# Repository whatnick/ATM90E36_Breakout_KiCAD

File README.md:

# ATM90E3x Breakout / Devkit

Basic PCB for driver development and experimenting with the the ATM90E3x series of energy monitor ASICS.
This is the KiCAD port of the original [Eagle PCB](https://github.com/whatnick/ATM90E36_Breakout).

Arduino Drivers are available [here](https://github.com/whatnick/ATM90E32_Arduino), maintained by [CircuitSetup](https://github.com/CircuitSetup). Also checkout the [Split Single-phase Energy Monitor](https://github.com/CircuitSetup/Split-Single-Phase-Energy-Meter).

## Features
- x4 3.5mm Stereo Jacks for 3-phase + Neutral current clamps
- 12v AC 3-phase transformer input for voltage measurement
- All pins broken out for deep integration including DMA mode for ATM90E36

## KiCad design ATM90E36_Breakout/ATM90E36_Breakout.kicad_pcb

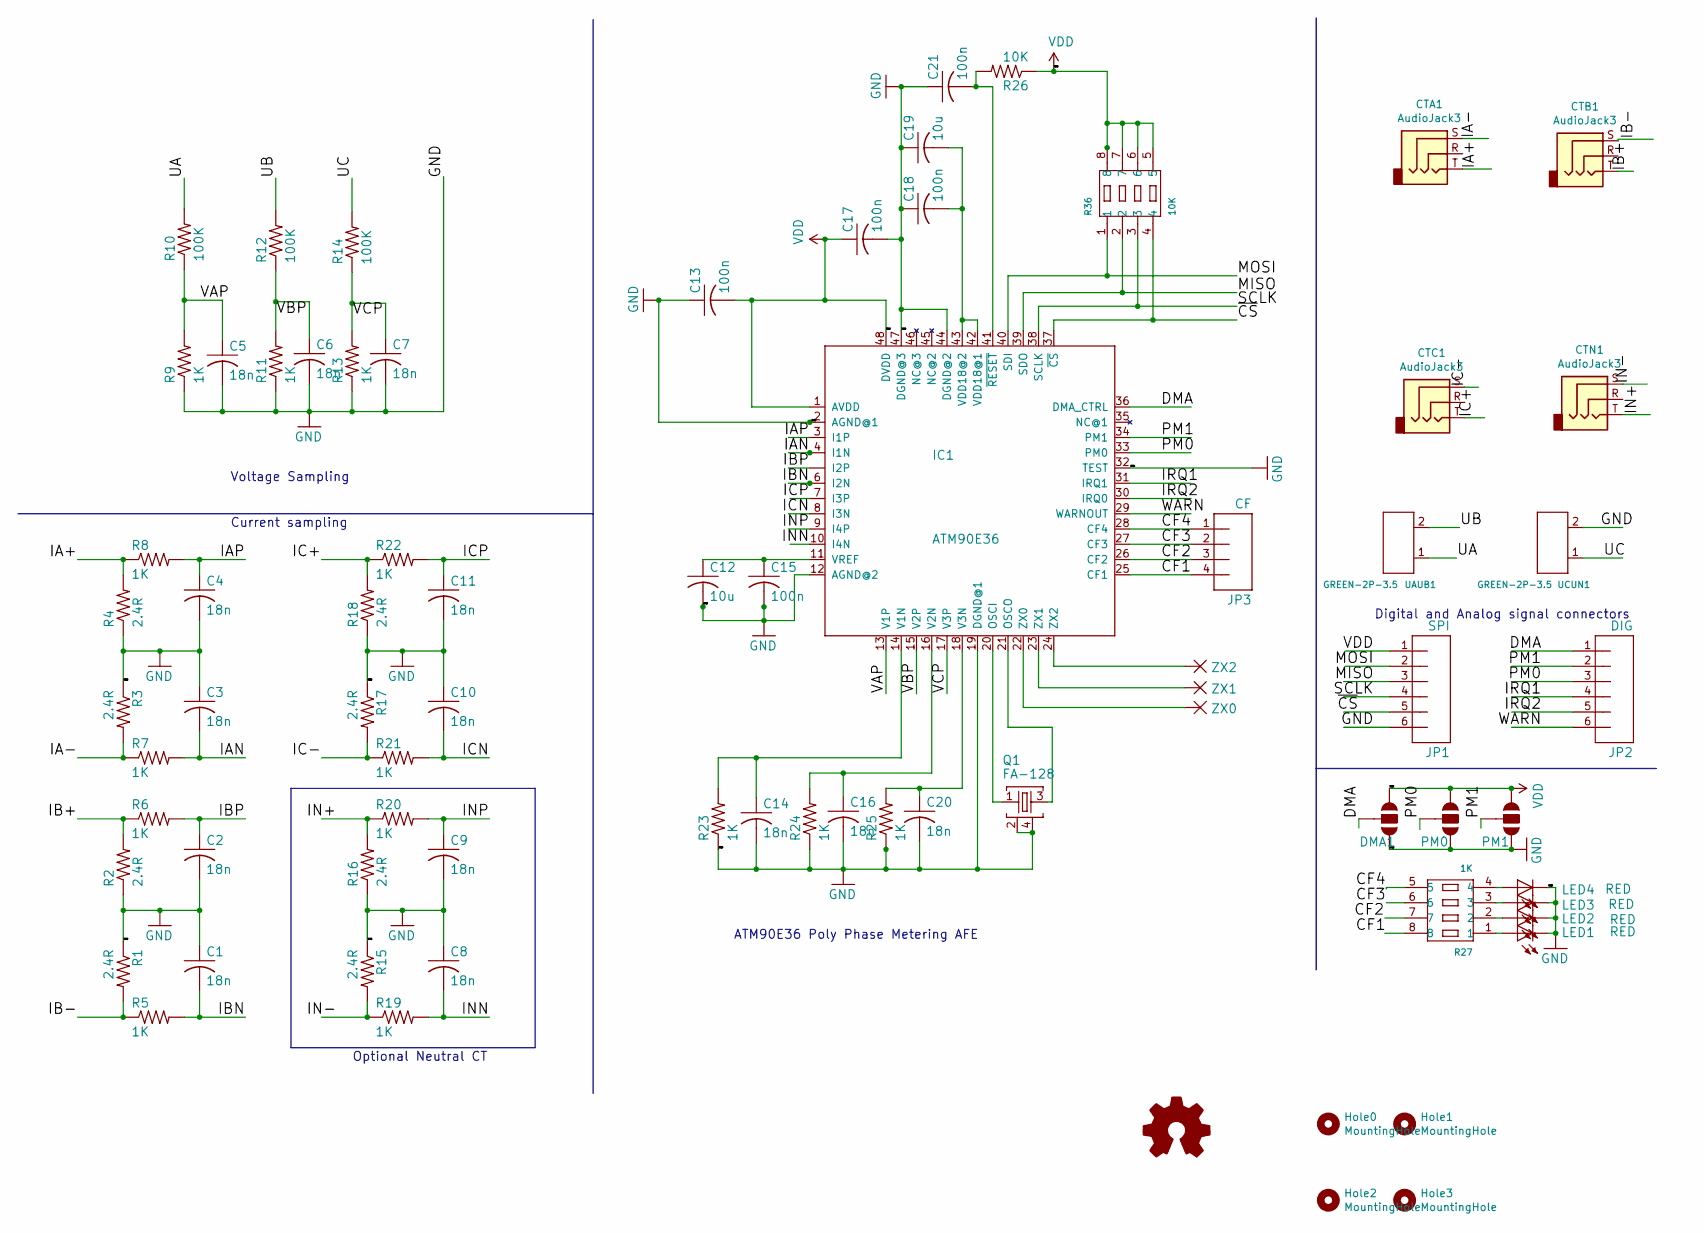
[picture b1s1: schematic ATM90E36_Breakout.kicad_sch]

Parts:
C1, C2, C3, C4, C5, C6, C7, C8, C9, C10, C11, C14, C16, C20: 18n; C0603
C12, C19: 10u; C0805
C13, C15, C17, C18, C21: 100n; C0603
CTA1: AudioJack3; Jack_3.5mm_CUI_SJ-3523-SMT_Horizontal
CTB1: AudioJack3; Jack_3.5mm_CUI_SJ-3523-SMT_Horizontal
CTC1: AudioJack3; Jack_3.5mm_CUI_SJ-3523-SMT_Horizontal
CTN1: AudioJack3; Jack_3.5mm_CUI_SJ-3523-SMT_Horizontal
DMA1: JUMPER-PAD-3-NOFULL_BOX_SILK; PAD-JUMPER-3-NO_YES_SILK_FULL_BOX
Hole0, Hole1, Hole2, Hole3: MountingHole; MountingHole_2.2mm_M2
IC1: ATM90E36; TQFP48
JP1: SPI; 1X06_LOCK
JP2: DIG; 1X06_LOCK
JP3: CF; 1X04_LOCK
LED1, LED2, LED3, LED4: RED; CHIP-LED0603
LOGO1: Logo_Open_Hardware_Small; OSHW-LOGO-M
PM0, PM1: JUMPER-PAD-3-NOFULL_BOX_SILK; PAD-JUMPER-3-NO_YES_SILK_FULL_BOX
Q1: FA-128
R1, R2, R3, R4, R15, R16, R17, R18: 2.4R; R0603
R5, R6, R7, R8, R9, R11, R13, R19, R20, R21, R22, R23, R24, R25: 1K; R0603
R10, R12, R14: 100K; R0603
R26: 10K; R0603
R27: 1K; RA1206-8
R36: 10K; RA1206-8
UAUB1: GREEN-2P-3.5; H2-3.5-7.0X7.0MM
UCUN1: GREEN-2P-3.5; H2-3.5-7.0X7.0MM
ZX0, ZX1, ZX2: ZX; SMD1,27-2,54

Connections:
/CF1: IC1.25 (CF1), JP3.4, R27.8
/CF2: IC1.26 (CF2), JP3.3, R27.7
/CF3: IC1.27 (CF3), JP3.2, R27.6
/CF4: IC1.28 (CF4), JP3.1, R27.5
/DMA: DMA1.2, IC1.36 (DMA_CTRL), JP2.1
/IA+: CTA1.T, R4.2, R8.1
/IA-: CTA1.S, R3.2, R7.1
/IAN: C3.2, IC1.4 (I1N), R7.2
/IAP: C4.1, IC1.3 (I1P), R8.2
/IB+: CTB1.T, R2.2, R6.1
/IB-: CTB1.S, R1.2, R5.1
/IBN: C1.2, IC1.6 (I2N), R5.2
/IBP: C2.1, IC1.5 (I2P), R6.2
/IC+: CTC1.T, R18.2, R22.1
/IC-: CTC1.S, R17.2, R21.1
/ICN: C10.2, IC1.8 (I3N), R21.2
/ICP: C11.1, IC1.7 (I3P), R22.2
/IN+: CTN1.T, R16.2, R20.1
/IN-: CTN1.S, R15.2, R19.1
/INN: C8.2, IC1.10 (I4N), R19.2
/INP: C9.1, IC1.9 (I4P), R20.2
/IRQ1: IC1.31 (IRQ1), JP2.4
/IRQ2: IC1.30 (IRQ0), JP2.5
/MISO: IC1.39 (SDO), JP1.3, R36.2
/MOSI: IC1.40 (SDI), JP1.2, R36.1
/PM0: IC1.33 (PM0), JP2.3, PM0.2
/PM1: IC1.34 (PM1), JP2.2, PM1.2
/SCLK: IC1.38 (SCLK), JP1.4, R36.3
/UA: R10.2, UAUB1.1
/UB: R12.2, UAUB1.2
/UC: R14.2, UCUN1.1
/VAP: C5.1, IC1.13 (V1P), R9.2, R10.1
/VBP: C6.1, IC1.15 (V2P), R11.2, R12.1
/VCP: C7.1, IC1.17 (V3P), R13.2, R14.1
/WARN: IC1.29 (WARNOUT), JP2.6
/~CS: IC1.37 (~CS), JP1.5, R36.4
GND: C1.1, C2.2, C3.1, C4.2, C5.2, C6.2, C7.2, C8.1, C9.2, C10.1, C11.2, C12.2, C13.1, C14.2, C15.2, C16.2, C17.2, C18.1, C19.1, C20.2, C21.1, DMA1.3, IC1.2 (AGND@1), IC1.12 (AGND@2), IC1.19 (DGND@1), IC1.32 (TEST), IC1.44 (DGND@2), IC1.47 (DGND@3), JP1.6, LED1.C, LED2.C, LED3.C, LED4.C, PM0.3, PM1.3, Q1.2, Q1.4, R1.1, R2.1, R3.1, R4.1, R9.1, R11.1, R13.1, R15.1, R16.1, R17.1, R18.1, R23.1, R24.1, R25.1, UCUN1.2
unnamed: C12.1, C15.1, IC1.11 (VREF)
unnamed: C14.1, IC1.14 (V1N), R23.2
unnamed: C16.1, IC1.16 (V2N), R24.2
unnamed: C18.2, C19.2, IC1.42 (VDD18@1), IC1.43 (VDD18@2)
unnamed: C20.1, IC1.18 (V3N), R25.2
unnamed: C21.2, IC1.41 (~RESET), R26.2
unnamed: IC1.20 (OSCI), Q1.1
unnamed: IC1.21 (OSCO), Q1.3
unnamed: IC1.22 (ZX0), ZX0.1
unnamed: IC1.23 (ZX1), ZX1.1
unnamed: IC1.24 (ZX2), ZX2.1
unnamed: LED1.A, R27.1
unnamed: LED2.A, R27.2
unnamed: LED3.A, R27.3
unnamed: LED4.A, R27.4
VDD: C13.2, C17.1, DMA1.1, IC1.1 (AVDD), IC1.48 (DVDD), JP1.1, PM0.1, PM1.1, R26.1, R36.5, R36.6, R36.7, R36.8

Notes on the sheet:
ATM90E36 Poly Phase Metering AFE
Optional Neutral CT
Voltage Sampling
Current sampling
Digital and Analog signal connectors

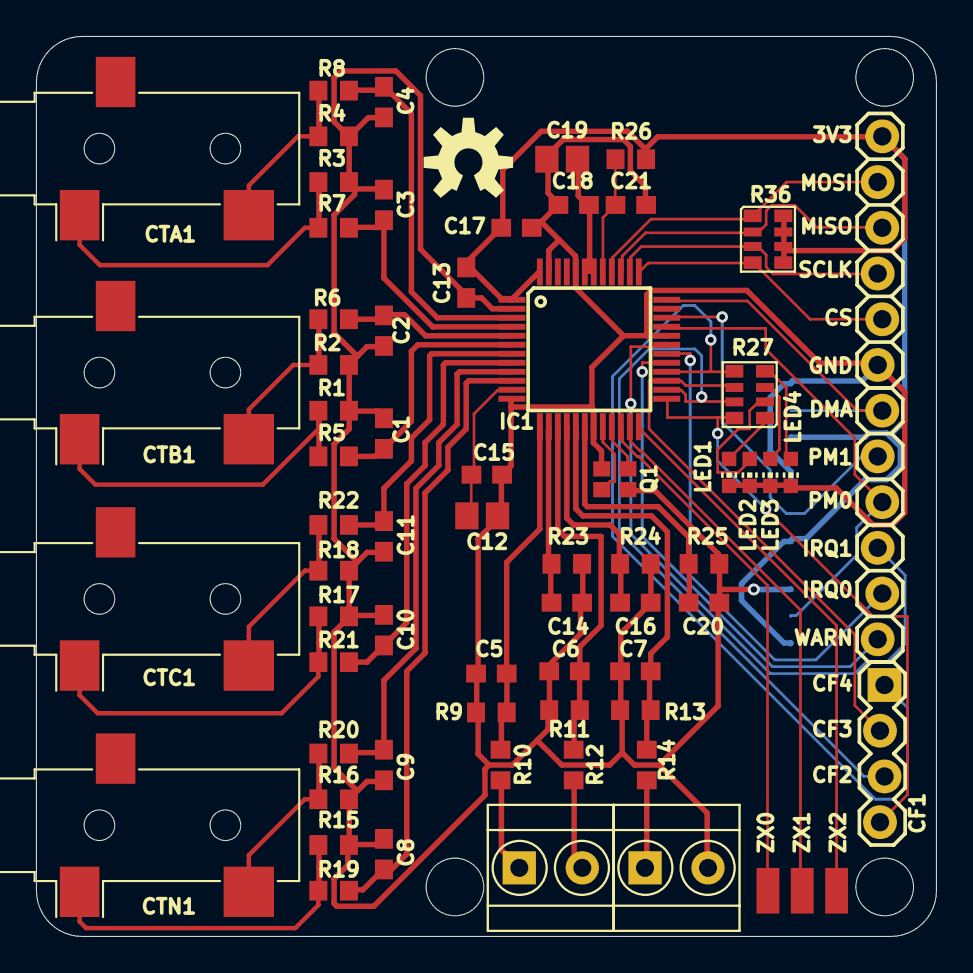
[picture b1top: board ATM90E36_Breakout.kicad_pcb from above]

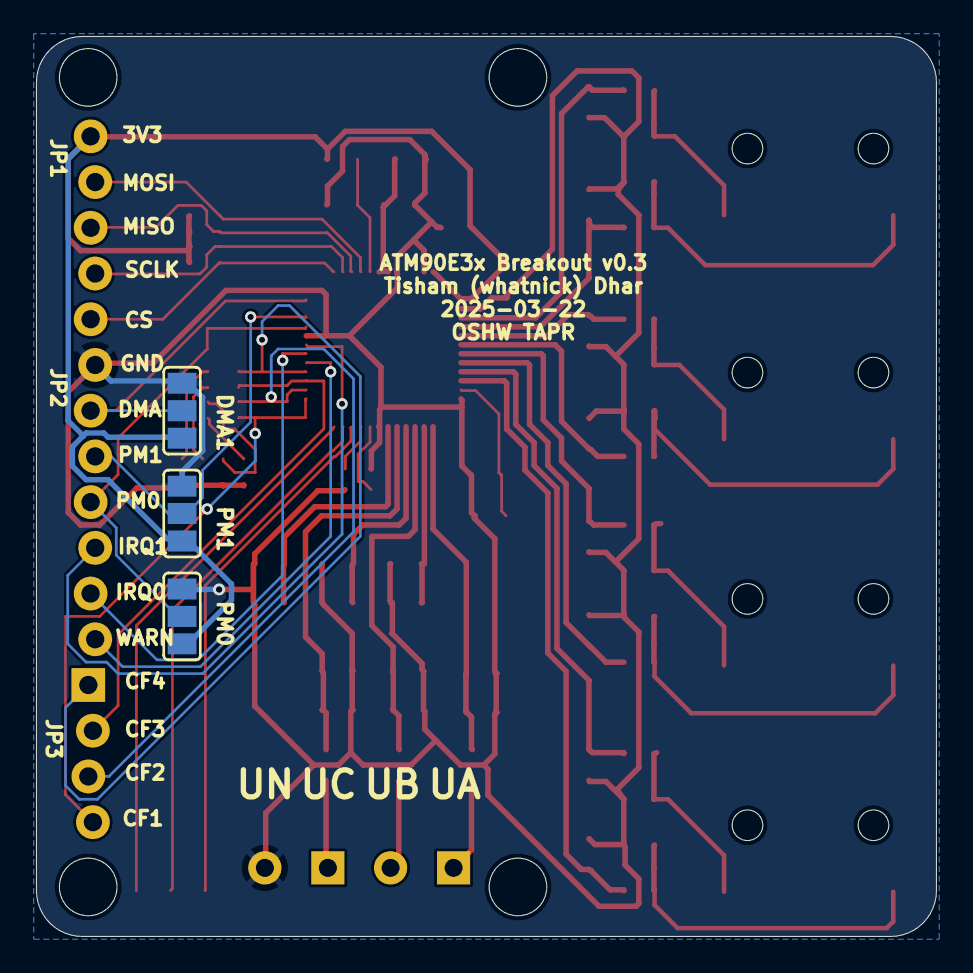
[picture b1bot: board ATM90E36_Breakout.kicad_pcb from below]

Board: 2 copper layers, 50.0 x 50.0 mm, 75 parts (3 on the bottom side), 53 nets.

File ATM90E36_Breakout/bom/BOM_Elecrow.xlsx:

*Reference | *Manufacturer Part number | *QTY | *Original | Description | Purchase Link
C13, C15, C17, C18, C21 | C0603C104K5RAC3190 | 5 | N | 100n
C1, C2, C3, C4, C5, C6, C7, C8, C9, C10, C11, C14, C16, C20 | C0603C183K5RACTU | 14 | N | 18n
C12, C19 | GRM21BR61E106MA73L | 2 | N | 10u
R1, R2, R3, R4, R15, R16, R17, R18 | CRL0603-FW-2R40ELF | 8 | N | 2.4R
R26 | RC0201JR-0710KL | 1 | N | 10K
R10, R12, R14 | RC0603FR-07100KL | 3 | N | 100K
R5, R6, R7, R8, R9, R11, R13, R19, R20, R21, R22, R23, R24, R25 | RT0603FRE071KL | 14 | N | 1K
R36 | YC164-JR-0710KL | 1 | N | 10K
R27 | YC164-JR-071KL | 1 | N | 1K
IC1 | ATM90E36A-AU-R | 1 | Y | ATM90E36A-AU-R
UAUB1, UCUN1 | 20020327-C021B01LF | 2 | N | GREEN-2P-3.5
Q1 | ECS-160-10-36-CKM-TR | 1 | Y | FA-128
LED1, LED2, LED3, LED4 | LTST-C193KRKT-5A | 4 | N | RED
CTA1, CTB1, CTC1, CTN1 | SJ-3523-SMT-TR | 4 | Y | AudioJack3

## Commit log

2019-12-23 Initial Import from Eagle
2019-12-23 Fix references and SCH/PCB linkage
2019-12-23 Remove edge cuts from parts to fix board outline
2019-12-25 Fix up silk screens
2019-12-30 Add full BOM and Gerbers
2019-12-31 Add BOM and dimensions for production prep
2020-01-04 Update parts for availability
2020-01-08 Updated Stereojacks to mainstream ones
2020-01-08 Updated Excel BOM
2020-01-08 Squash fab file packs
2020-02-20 Fix BOM part
2024-08-18 Upgrade to KiCAD 7 and order from Elecrow
2025-03-22 Update silkscreen to avoid wiring confusion
2025-03-22 deleted old outputs
